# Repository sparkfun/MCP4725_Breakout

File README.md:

MCP4725_Breakout
================
[  
*Breakout Board for MCP4725 I2C DAC (BOB-12918)*](https://www.sparkfun.com/products/12918)

The MCP4725 is an I<sup>2</sup>C controlled Digital-to-Analog converter (DAC). It allows you to send an analog signal from a digital source.

Repository Contents
-------------------
* **/Hardware** - Eagle PCB layout files
* **/Production** - Test bed files and production panel files

Version History
---------------
* [BOB-08736](https://www.sparkfun.com/products/8736) -Version 1.3. Now retired. 

License Information
-------------------
The hardware is released under [Creative Commons ShareAlike 4.0 International](https://creativecommons.org/licenses/by-sa/4.0/).
The code is beerware; if you see me (or any other SparkFun employee) at the local, and you've found our code helpful, please buy us a round!

Distributed as-is; no warranty is given.

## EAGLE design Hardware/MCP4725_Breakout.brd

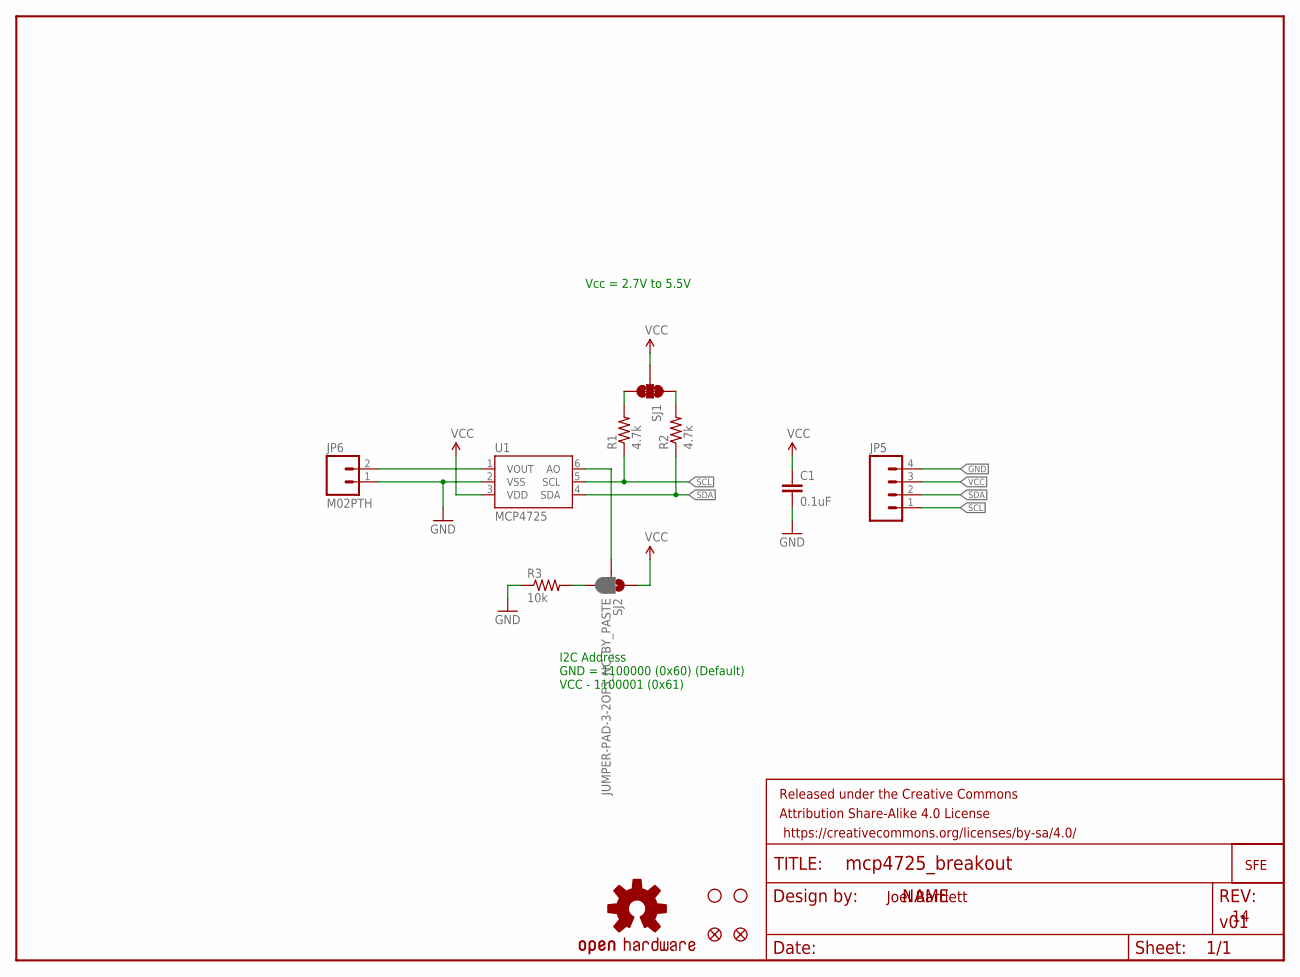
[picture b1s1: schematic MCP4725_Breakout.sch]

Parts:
C1: 0.1uF; 0603-CAP
FID1, FID2: FIDUCIAL1X2; FIDUCIAL-1X2
FRAME2: FRAME-LETTER; CREATIVE_COMMONS
GND: LOGO-SFESK; SFE-LOGO-FLAME
JP5: M04PTH; 1X04
JP6: M02PTH; 1X02
LOGO1: OSHW-LOGOS; OSHW-LOGO-S
R1, R2: 4.7k; 0603-RES
R3: 10k; 0603-RES
SJ1: JUMPER-PAD-3-NC_BY_TRACE; PAD-JUMPER-3-3OF3_NC_BY_TRACE_YES_SILK_FULL_BOX
SJ2: JUMPER-PAD-3-2OF3_NC_BY_PASTE; PAD-JUMPER-3-2OF3_NC_BY_PASTE_YES_SILK_FULL_BOX
STANDOFF1, STANDOFF2: STAND-OFF
U1: MCP4725; SOT23-6

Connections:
GND: C1.2, JP5.4, JP6.1, R3.1, U1.2 (VSS)
unnamed: R2.2, SJ1.1
unnamed: R1.2, SJ1.3
unnamed: SJ2.2, U1.6 (AO)
unnamed: R3.2, SJ2.3
SCL: JP5.1, R1.1, U1.5 (SCL)
SDA: JP5.2, R2.1, U1.4 (SDA)
VCC: C1.1, JP5.3, SJ1.2, SJ2.1, U1.3 (VDD)
VOUT: JP6.2, U1.1 (VOUT)

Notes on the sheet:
I2C Address GND = 1100000 (0x60) (Default) VCC - 1100001 (0x61)
Joel Bartlett
Vcc = 2.7V to 5.5V

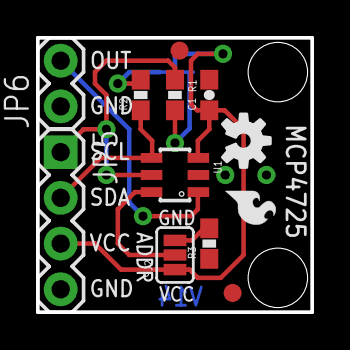
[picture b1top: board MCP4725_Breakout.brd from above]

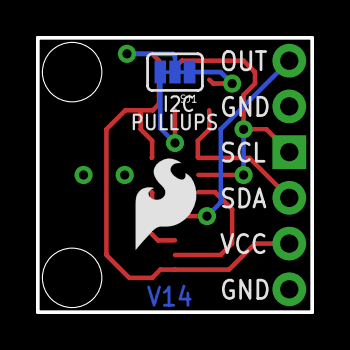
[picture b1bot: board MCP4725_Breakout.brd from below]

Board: 2 copper layers, 15.2 x 15.2 mm, 17 parts (2 on the bottom side), 9 nets.

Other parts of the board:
U$3: SFE_LOGO_FLAME_.2

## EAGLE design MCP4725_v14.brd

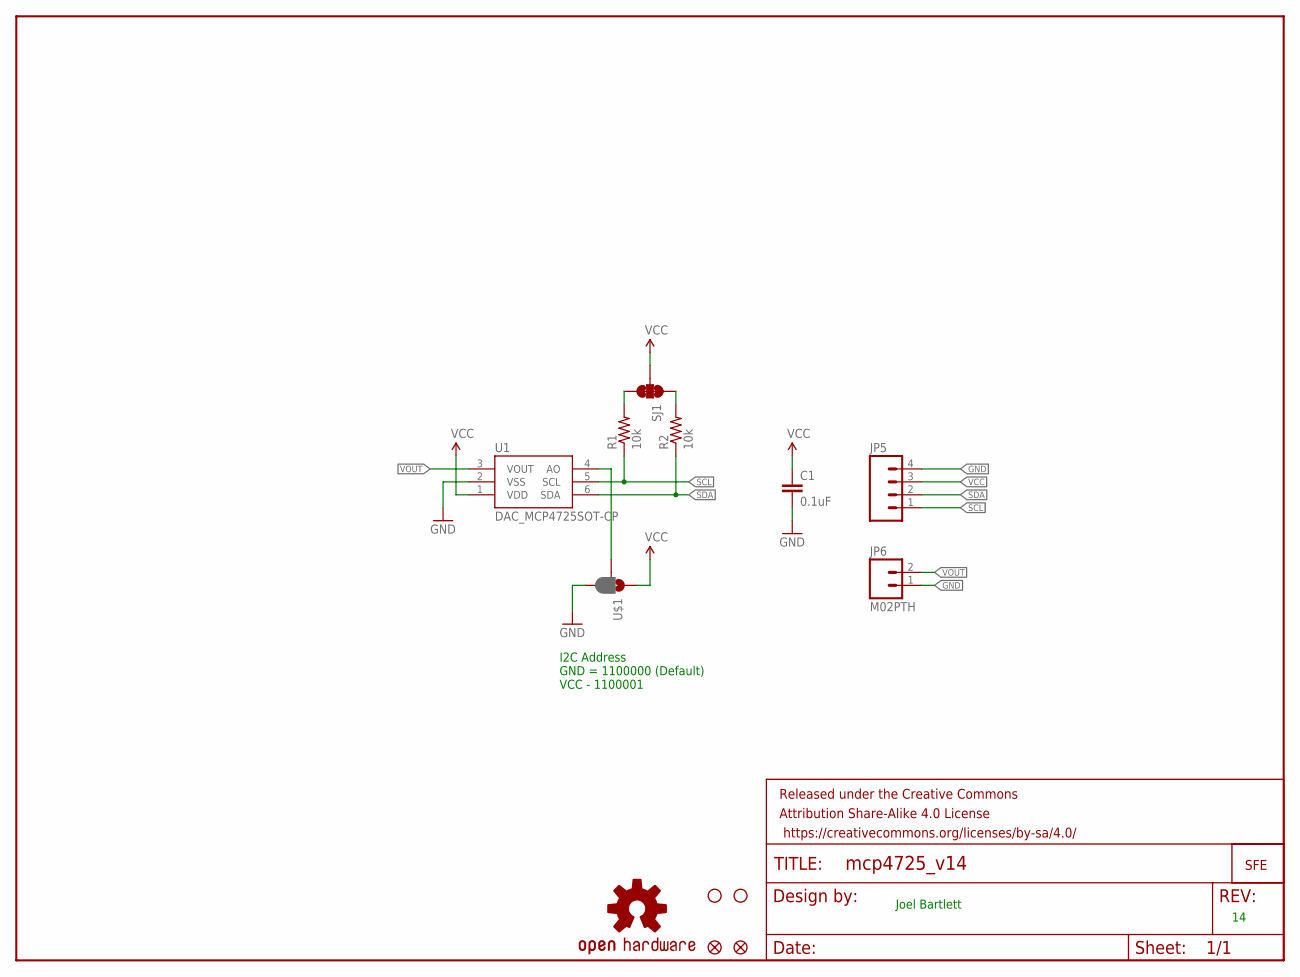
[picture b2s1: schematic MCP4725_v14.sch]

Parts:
C1: 0.1uF; 0603-CAP
FRAME2: FRAME-LETTER; CREATIVE_COMMONS
GND: LOGO-SFESK; SFE-LOGO-FLAME
JP2, JP3: FIDUCIALUFIDUCIAL; MICRO-FIDUCIAL
JP5: M04PTH; 1X04
JP6: M02PTH; 1X02
LOGO1: OSHW-LOGOS; OSHW-LOGO-S
R1, R2: 10k; 0603-RES
SJ1: JUMPER-PAD-3-NC_BY_TRACE; PAD-JUMPER-3-3OF3_NC_BY_TRACE_YES_SILK_FULL_BOX
STANDOFF1, STANDOFF2: STAND-OFF
U1: DAC_MCP4725SOT-CP; SOT23-6-MCP4725
U$1: JUMPER-PAD-3-2OF3_NC_BY_PASTE; PAD-JUMPER-3-2OF3_NC_BY_PASTE_YES_SILK_FULL_BOX

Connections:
GND: C1.2, JP5.4, JP6.1, U1.2 (VSS), U$1.3
unnamed: R2.2, SJ1.1
unnamed: R1.2, SJ1.3
unnamed: U1.4 (AO), U$1.2
SCL: JP5.1, R1.1, U1.5 (SCL)
SDA: JP5.2, R2.1, U1.6 (SDA)
VCC: C1.1, JP5.3, SJ1.2, U1.1 (VDD), U$1.1
VOUT: JP6.2, U1.3 (VOUT)

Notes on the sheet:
I2C Address GND = 1100000 (Default) VCC - 1100001
Joel Bartlett

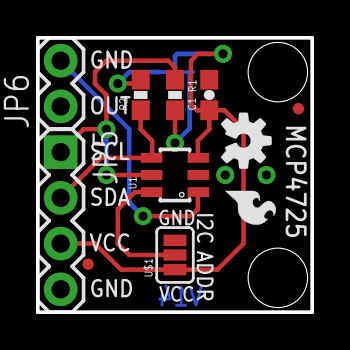
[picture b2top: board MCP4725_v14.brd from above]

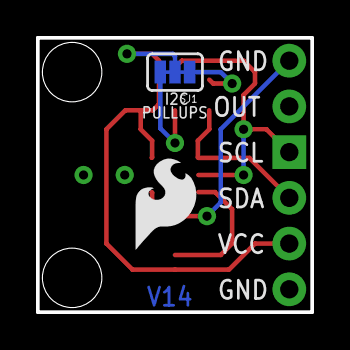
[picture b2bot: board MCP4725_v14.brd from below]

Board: 2 copper layers, 15.2 x 15.2 mm, 16 parts (2 on the bottom side), 8 nets.

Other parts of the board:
U$3: SFE_LOGO_FLAME_.2

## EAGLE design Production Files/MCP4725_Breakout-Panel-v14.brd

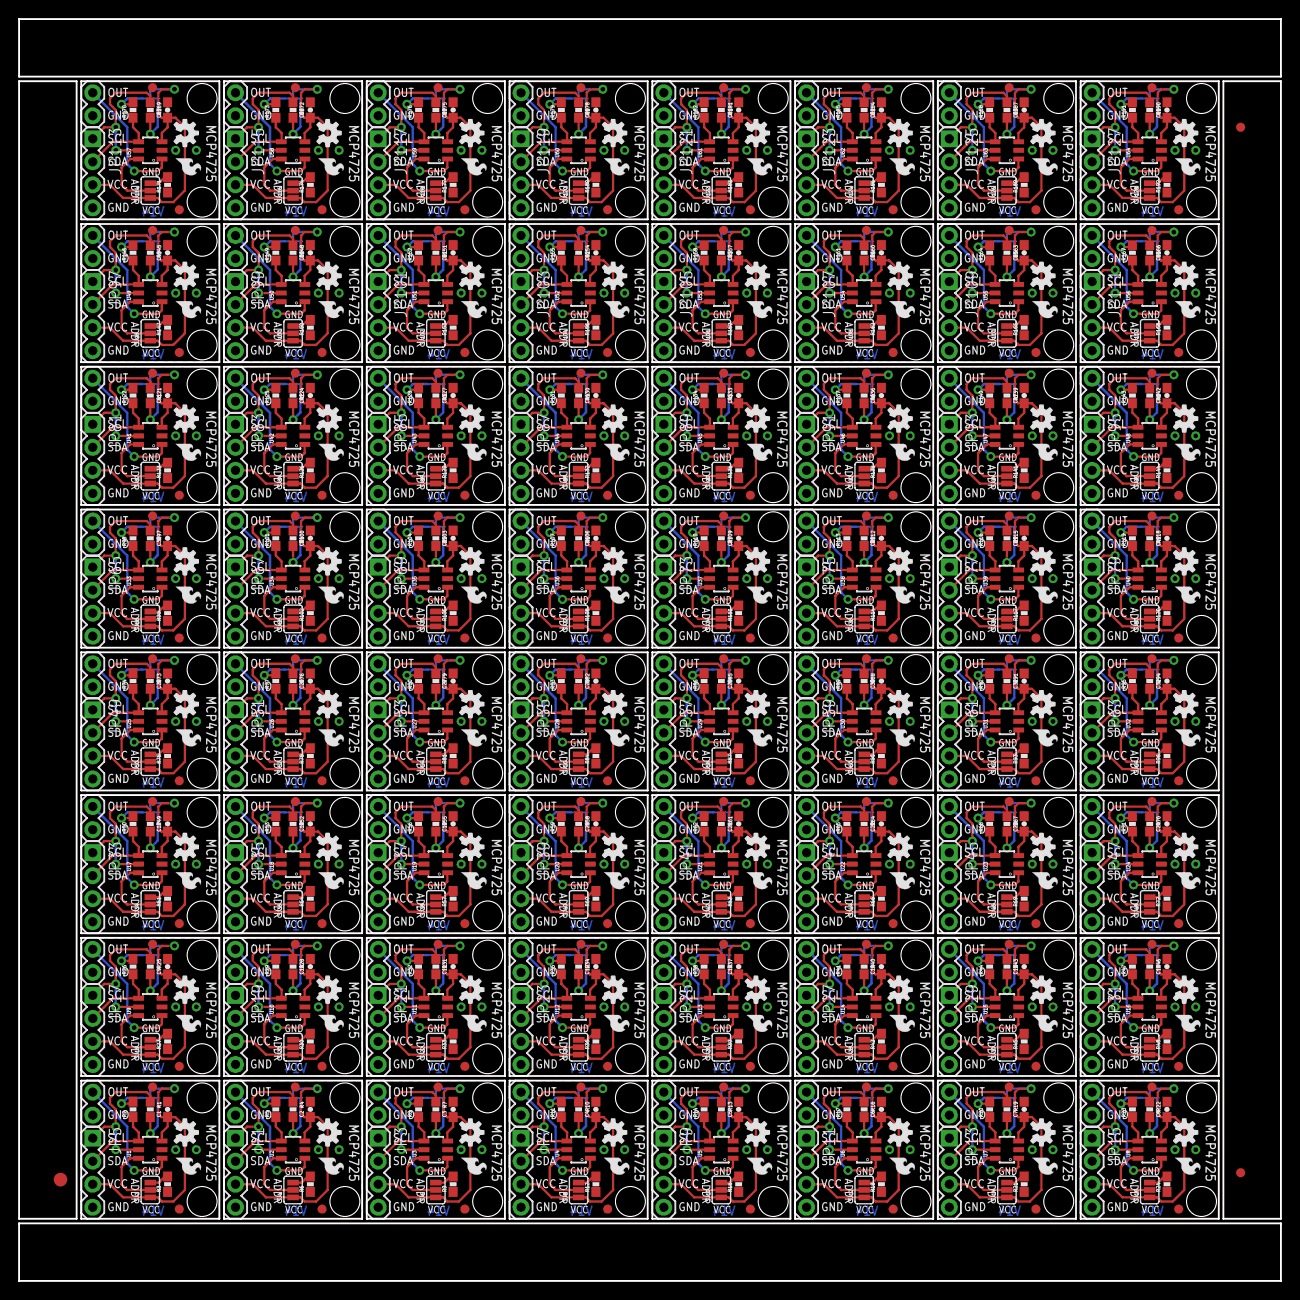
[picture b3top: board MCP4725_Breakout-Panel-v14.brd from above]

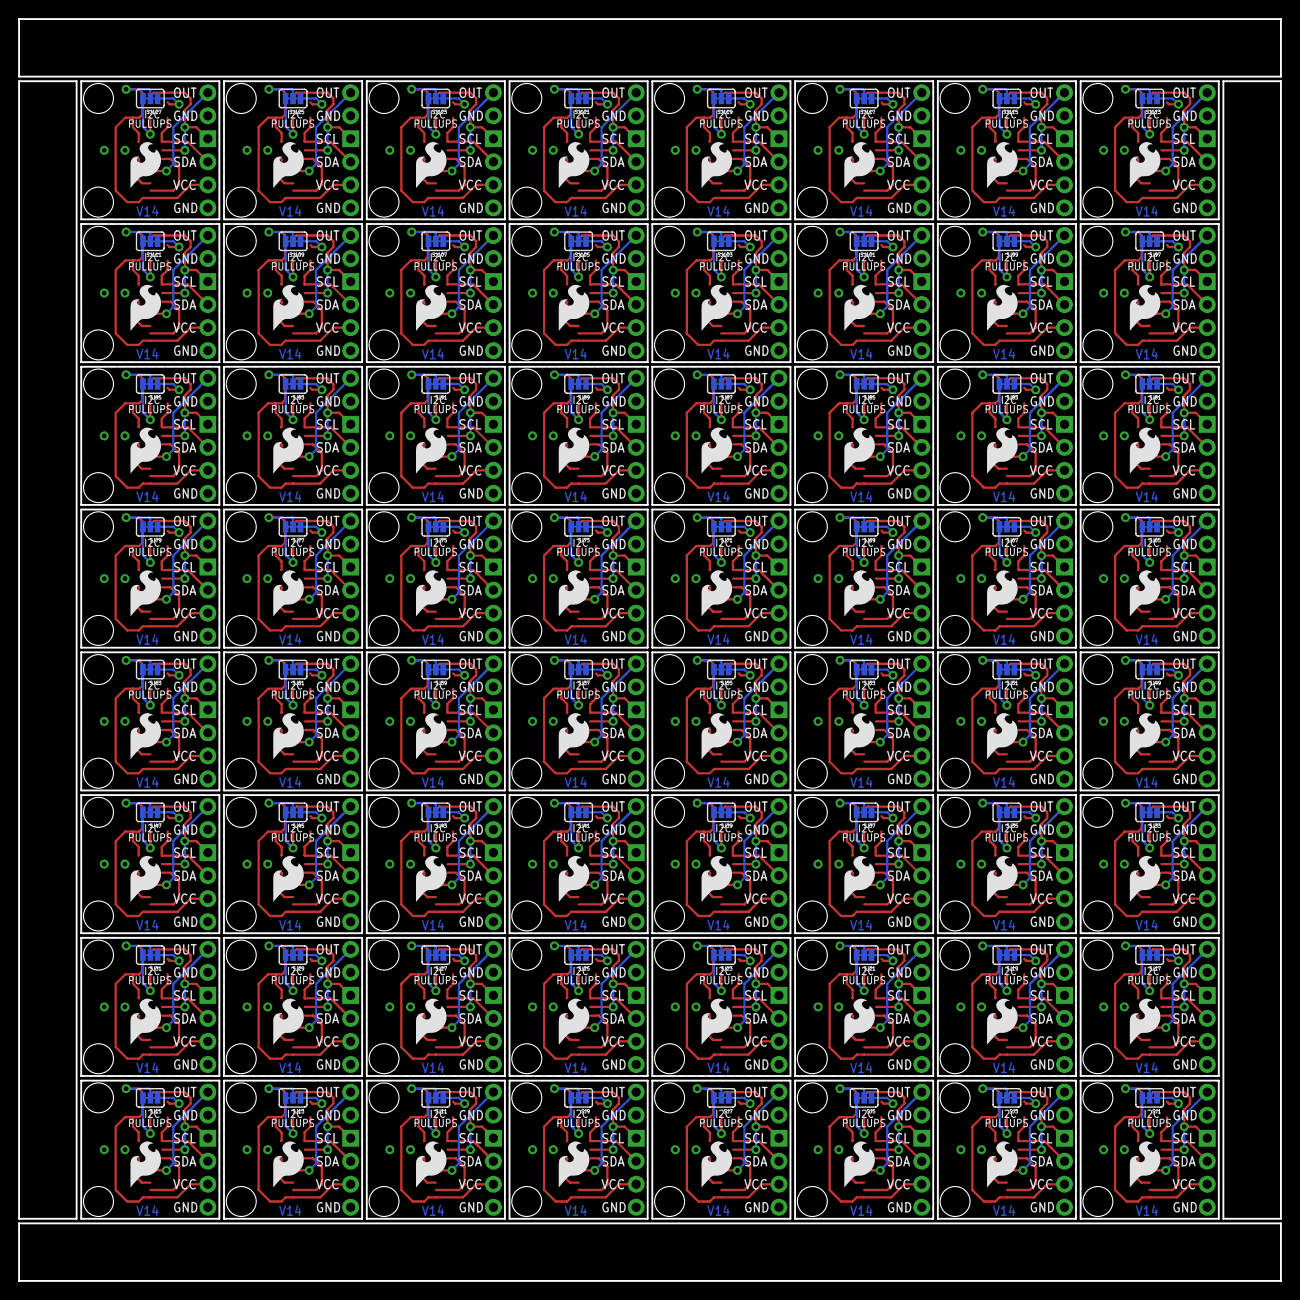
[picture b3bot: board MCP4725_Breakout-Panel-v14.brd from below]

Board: 2 copper layers, 139.2 x 139.2 mm, 1027 parts (128 on the bottom side), 576 nets.

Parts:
C1, C2, C3, C4, C5, C6, C7, C8, C9, C10, C11, C12, C13, C14, C15, C16, C17, C18, C19, C20, C21, C22, C23, C24, C25, C26, C27, C28, C29, C30, C31, C32, C33, C34, C35, C36, C37, C38, C39, C40, C41, C42, C43, C44, C45, C46, C47, C48, C49, C50, C51, C52, C53, C54, C55, C56, C57, C58, C59, C60, C61, C62, C63, C64: 0.1uF; 0603-CAP
E$1: FIDUCIAL-1.5X3
E$4, E$5: FIDUCIAL-1X2
FID1, FID2, FID3, FID4, FID5, FID6, FID7, FID8, FID9, FID10, FID11, FID12, FID13, FID14, FID15, FID16, FID17, FID18, FID19, FID20, FID21, FID22, FID23, FID24, FID25, FID26, FID27, FID28, FID29, FID30, FID31, FID32, FID33, FID34, FID35, FID36, FID37, FID38, FID39, FID40, FID41, FID42, FID43, FID44, FID45, FID46, FID47, FID48, FID49, FID50, FID51, FID52, FID53, FID54, FID55, FID56, FID57, FID58, FID59, FID60, FID61, FID62, FID63, FID64, FID65, FID66, FID67, FID68, FID69, FID70, FID71, FID72, FID73, FID74, FID75, FID76, FID77, FID78, FID79, FID80, FID81, FID82, FID83, FID84, FID85, FID86, FID87, FID88, FID89, FID90, FID91, FID92, FID93, FID94, FID95, FID96, FID97, FID98, FID99, FID100, FID101, FID102, FID103, FID104, FID105, FID106, FID107, FID108, FID109, FID110, FID111, FID112, FID113, FID114, FID115, FID116, FID117, FID118, FID119, FID120, FID121, FID122, FID123, FID124, FID125, FID126, FID127, FID128: FIDUCIAL1X2; FIDUCIAL-1X2
GND, GND1, GND2, GND3, GND4, GND5, GND6, GND7, GND8, GND9, GND10, GND11, GND12, GND13, GND14, GND15, GND16, GND17, GND18, GND19, GND20, GND21, GND22, GND23, GND24, GND25, GND26, GND27, GND28, GND29, GND30, GND31, GND32, GND33, GND34, GND35, GND36, GND37, GND38, GND39, GND40, GND41, GND42, GND43, GND44, GND45, GND46, GND47, GND48, GND49, GND50, GND51, GND52, GND53, GND54, GND55, GND56, GND57, GND58, GND59, GND60, GND61, GND62, GND63: LOGO-SFESK; SFE-LOGO-FLAME
JP1, JP3, JP5, JP7, JP9, JP11, JP13, JP15, JP17, JP19, JP21, JP23, JP25, JP27, JP29, JP31, JP33, JP35, JP37, JP39, JP41, JP43, JP45, JP47, JP49, JP51, JP53, JP55, JP57, JP59, JP61, JP63, JP65, JP67, JP69, JP71, JP73, JP75, JP77, JP79, JP81, JP83, JP85, JP87, JP89, JP91, JP93, JP95, JP97, JP99, JP101, JP103, JP105, JP107, JP109, JP111, JP113, JP115, JP117, JP119, JP121, JP123, JP125, JP127: 1X04
JP2, JP4, JP6, JP8, JP10, JP12, JP14, JP16, JP18, JP20, JP22, JP24, JP26, JP28, JP30, JP32, JP34, JP36, JP38, JP40, JP42, JP44, JP46, JP48, JP50, JP52, JP54, JP56, JP58, JP60, JP62, JP64, JP66, JP68, JP70, JP72, JP74, JP76, JP78, JP80, JP82, JP84, JP86, JP88, JP90, JP92, JP94, JP96, JP98, JP100, JP102, JP104, JP106, JP108, JP110, JP112, JP114, JP116, JP118, JP120, JP122, JP124, JP126, JP128: M02PTH; 1X02
LOGO1, LOGO2, LOGO3, LOGO4, LOGO5, LOGO6, LOGO7, LOGO8, LOGO9, LOGO10, LOGO11, LOGO12, LOGO13, LOGO14, LOGO15, LOGO16, LOGO17, LOGO18, LOGO19, LOGO20, LOGO21, LOGO22, LOGO23, LOGO24, LOGO25, LOGO26, LOGO27, LOGO28, LOGO29, LOGO30, LOGO31, LOGO32, LOGO33, LOGO34, LOGO35, LOGO36, LOGO37, LOGO38, LOGO39, LOGO40, LOGO41, LOGO42, LOGO43, LOGO44, LOGO45, LOGO46, LOGO47, LOGO48, LOGO49, LOGO50, LOGO51, LOGO52, LOGO53, LOGO54, LOGO55, LOGO56, LOGO57, LOGO58, LOGO59, LOGO60, LOGO61, LOGO62, LOGO63, LOGO64: OSHW-LOGOS; OSHW-LOGO-S
R1, R2, R4, R5, R7, R8, R10, R11, R13, R14, R16, R17, R19, R20, R22, R23, R25, R26, R28, R29, R31, R32, R34, R35, R37, R38, R40, R41, R43, R44, R46, R47, R49, R50, R52, R53, R55, R56, R58, R59, R61, R62, R64, R65, R67, R68, R70, R71, R73, R74, R76, R77, R79, R80, R82, R83, R85, R86, R88, R89, R91, R92, R94, R95, R97, R98, R100, R101, R103, R104, R106, R107, R109, R110, R112, R113, R115, R116, R118, R119, R121, R122, R124, R125, R127, R128, R130, R131, R133, R134, R136, R137, R139, R140, R142, R143, R145, R146, R148, R149, R151, R152, R154, R155, R157, R158, R160, R161, R163, R164, R166, R167, R169, R170, R172, R173, R175, R176, R178, R179, R181, R182, R184, R185, R187, R188, R190, R191: 4.7k; 0603-RES
R3, R6, R9, R12, R15, R18, R21, R24, R27, R30, R33, R36, R39, R42, R45, R48, R51, R54, R57, R60, R63, R66, R69, R72, R75, R78, R81, R84, R87, R90, R93, R96, R99, R102, R105, R108, R111, R114, R117, R120, R123, R126, R129, R132, R135, R138, R141, R144, R147, R150, R153, R156, R159, R162, R165, R168, R171, R174, R177, R180, R183, R186, R189, R192: 10k; 0603-RES
SJ1, SJ3, SJ5, SJ7, SJ9, SJ11, SJ13, SJ15, SJ17, SJ19, SJ21, SJ23, SJ25, SJ27, SJ29, SJ31, SJ33, SJ35, SJ37, SJ39, SJ41, SJ43, SJ45, SJ47, SJ49, SJ51, SJ53, SJ55, SJ57, SJ59, SJ61, SJ63, SJ65, SJ67, SJ69, SJ71, SJ73, SJ75, SJ77, SJ79, SJ81, SJ83, SJ85, SJ87, SJ89, SJ91, SJ93, SJ95, SJ97, SJ99, SJ101, SJ103, SJ105, SJ107, SJ109, SJ111, SJ113, SJ115, SJ117, SJ119, SJ121, SJ123, SJ125, SJ127: PAD-JUMPER-3-3OF3_NC_BY_TRACE_YES_SILK_FULL_BOX
SJ2, SJ4, SJ6, SJ8, SJ10, SJ12, SJ14, SJ16, SJ18, SJ20, SJ22, SJ24, SJ26, SJ28, SJ30, SJ32, SJ34, SJ36, SJ38, SJ40, SJ42, SJ44, SJ46, SJ48, SJ50, SJ52, SJ54, SJ56, SJ58, SJ60, SJ62, SJ64, SJ66, SJ68, SJ70, SJ72, SJ74, SJ76, SJ78, SJ80, SJ82, SJ84, SJ86, SJ88, SJ90, SJ92, SJ94, SJ96, SJ98, SJ100, SJ102, SJ104, SJ106, SJ108, SJ110, SJ112, SJ114, SJ116, SJ118, SJ120, SJ122, SJ124, SJ126, SJ128: PAD-JUMPER-3-2OF3_NC_BY_PASTE_YES_SILK_FULL_BOX
STANDOFF1, STANDOFF2, STANDOFF3, STANDOFF4, STANDOFF5, STANDOFF6, STANDOFF7, STANDOFF8, STANDOFF9, STANDOFF10, STANDOFF11, STANDOFF12, STANDOFF13, STANDOFF14, STANDOFF15, STANDOFF16, STANDOFF17, STANDOFF18, STANDOFF19, STANDOFF20, STANDOFF21, STANDOFF22, STANDOFF23, STANDOFF24, STANDOFF25, STANDOFF26, STANDOFF27, STANDOFF28, STANDOFF29, STANDOFF30, STANDOFF31, STANDOFF32, STANDOFF33, STANDOFF34, STANDOFF35, STANDOFF36, STANDOFF37, STANDOFF38, STANDOFF39, STANDOFF40, STANDOFF41, STANDOFF42, STANDOFF43, STANDOFF44, STANDOFF45, STANDOFF46, STANDOFF47, STANDOFF48, STANDOFF49, STANDOFF50, STANDOFF51, STANDOFF52, STANDOFF53, STANDOFF54, STANDOFF55, STANDOFF56, STANDOFF57, STANDOFF58, STANDOFF59, STANDOFF60, STANDOFF61, STANDOFF62, STANDOFF63, STANDOFF64, STANDOFF65, STANDOFF66, STANDOFF67, STANDOFF68, STANDOFF69, STANDOFF70, STANDOFF71, STANDOFF72, STANDOFF73, STANDOFF74, STANDOFF75, STANDOFF76, STANDOFF77, STANDOFF78, STANDOFF79, STANDOFF80, STANDOFF81, STANDOFF82, STANDOFF83, STANDOFF84, STANDOFF85, STANDOFF86, STANDOFF87, STANDOFF88, STANDOFF89, STANDOFF90, STANDOFF91, STANDOFF92, STANDOFF93, STANDOFF94, STANDOFF95, STANDOFF96, STANDOFF97, STANDOFF98, STANDOFF99, STANDOFF100, STANDOFF101, STANDOFF102, STANDOFF103, STANDOFF104, STANDOFF105, STANDOFF106, STANDOFF107, STANDOFF108, STANDOFF109, STANDOFF110, STANDOFF111, STANDOFF112, STANDOFF113, STANDOFF114, STANDOFF115, STANDOFF116, STANDOFF117, STANDOFF118, STANDOFF119, STANDOFF120, STANDOFF121, STANDOFF122, STANDOFF123, STANDOFF124, STANDOFF125, STANDOFF126, STANDOFF127, STANDOFF128: STAND-OFF
U1, U2, U3, U4, U5, U6, U7, U8, U9, U10, U11, U12, U13, U14, U15, U16, U17, U18, U19, U20, U21, U22, U23, U24, U25, U26, U27, U28, U29, U30, U31, U32, U33, U34, U35, U36, U37, U38, U39, U40, U41, U42, U43, U44, U45, U46, U47, U48, U49, U50, U51, U52, U53, U54, U55, U56, U57, U58, U59, U60, U61, U62, U63, U64: DAC_MCP4725SOT-CP; SOT23-6-MCP4725
U$1, U$2, U$3, U$4, U$5, U$6, U$7, U$8, U$9, U$10, U$11, U$12, U$13, U$14, U$15, U$16, U$17, U$18, U$19, U$20, U$21, U$22, U$23, U$24, U$25, U$26, U$27, U$28, U$29, U$30, U$31, U$32, U$33, U$34, U$35, U$36, U$37, U$38, U$39, U$40, U$41, U$42, U$43, U$44, U$45, U$46, U$47, U$48, U$49, U$50, U$51, U$52, U$53, U$54, U$55, U$56, U$57, U$58, U$59, U$60, U$61, U$62, U$63, U$64: SFE_LOGO_FLAME_.2

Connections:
GND: C1.2, JP5.4, JP6.1, R3.1, U1.2
GND1: C2.2, JP1.4, JP2.1, R6.1, U2.2
GND2: C3.2, JP3.4, JP4.1, R9.1, U3.2
GND3: C4.2, JP7.4, JP8.1, R12.1, U4.2
GND4: C5.2, JP9.4, JP10.1, R15.1, U5.2
GND5: C6.2, JP11.4, JP12.1, R18.1, U6.2
GND6: C7.2, JP13.4, JP14.1, R21.1, U7.2
GND7: C8.2, JP15.4, JP16.1, R24.1, U8.2
GND8: C9.2, JP17.4, JP18.1, R27.1, U9.2
GND9: C10.2, JP19.4, JP20.1, R30.1, U10.2
GND10: C11.2, JP21.4, JP22.1, R33.1, U11.2
GND11: C12.2, JP23.4, JP24.1, R36.1, U12.2
GND12: C13.2, JP25.4, JP26.1, R39.1, U13.2
GND13: C14.2, JP27.4, JP28.1, R42.1, U14.2
GND14: C15.2, JP29.4, JP30.1, R45.1, U15.2
GND15: C16.2, JP31.4, JP32.1, R48.1, U16.2
GND16: C17.2, JP33.4, JP34.1, R51.1, U17.2
GND17: C18.2, JP35.4, JP36.1, R54.1, U18.2
GND18: C19.2, JP37.4, JP38.1, R57.1, U19.2
GND19: C20.2, JP39.4, JP40.1, R60.1, U20.2
GND20: C21.2, JP41.4, JP42.1, R63.1, U21.2
GND21: C22.2, JP43.4, JP44.1, R66.1, U22.2
GND22: C23.2, JP45.4, JP46.1, R69.1, U23.2
GND23: C24.2, JP47.4, JP48.1, R72.1, U24.2
GND24: C25.2, JP49.4, JP50.1, R75.1, U25.2
GND25: C26.2, JP51.4, JP52.1, R78.1, U26.2
GND26: C27.2, JP53.4, JP54.1, R81.1, U27.2
GND27: C28.2, JP55.4, JP56.1, R84.1, U28.2
GND28: C29.2, JP57.4, JP58.1, R87.1, U29.2
GND29: C30.2, JP59.4, JP60.1, R90.1, U30.2
GND30: C31.2, JP61.4, JP62.1, R93.1, U31.2
GND31: C32.2, JP63.4, JP64.1, R96.1, U32.2
GND32: C33.2, JP65.4, JP66.1, R99.1, U33.2
GND33: C34.2, JP67.4, JP68.1, R102.1, U34.2
GND34: C35.2, JP69.4, JP70.1, R105.1, U35.2
GND35: C36.2, JP71.4, JP72.1, R108.1, U36.2
GND36: C37.2, JP73.4, JP74.1, R111.1, U37.2
GND37: C38.2, JP75.4, JP76.1, R114.1, U38.2
GND38: C39.2, JP77.4, JP78.1, R117.1, U39.2
GND39: C40.2, JP79.4, JP80.1, R120.1, U40.2
GND40: C41.2, JP81.4, JP82.1, R123.1, U41.2
GND41: C42.2, JP83.4, JP84.1, R126.1, U42.2
GND42: C43.2, JP85.4, JP86.1, R129.1, U43.2
GND43: C44.2, JP87.4, JP88.1, R132.1, U44.2
GND44: C45.2, JP89.4, JP90.1, R135.1, U45.2
GND45: C46.2, JP91.4, JP92.1, R138.1, U46.2
GND46: C47.2, JP93.4, JP94.1, R141.1, U47.2
GND47: C48.2, JP95.4, JP96.1, R144.1, U48.2
GND48: C49.2, JP97.4, JP98.1, R147.1, U49.2
GND49: C50.2, JP99.4, JP100.1, R150.1, U50.2
GND50: C51.2, JP101.4, JP102.1, R153.1, U51.2
GND51: C52.2, JP103.4, JP104.1, R156.1, U52.2
GND52: C53.2, JP105.4, JP106.1, R159.1, U53.2
GND53: C54.2, JP107.4, JP108.1, R162.1, U54.2
GND54: C55.2, JP109.4, JP110.1, R165.1, U55.2
GND55: C56.2, JP111.4, JP112.1, R168.1, U56.2
GND56: C57.2, JP113.4, JP114.1, R171.1, U57.2
GND57: C58.2, JP115.4, JP116.1, R174.1, U58.2
GND58: C59.2, JP117.4, JP118.1, R177.1, U59.2
GND59: C60.2, JP119.4, JP120.1, R180.1, U60.2
GND60: C61.2, JP121.4, JP122.1, R183.1, U61.2
GND61: C62.2, JP123.4, JP124.1, R186.1, U62.2
GND62: C63.2, JP125.4, JP126.1, R189.1, U63.2
GND63: C64.2, JP127.4, JP128.1, R192.1, U64.2
unnamed: R2.2, SJ1.1
unnamed: R1.2, SJ1.3
unnamed: SJ2.2, U1.4
unnamed: R3.2, SJ2.3
unnamed: R5.2, SJ3.1
unnamed: R4.2, SJ3.3
unnamed: SJ4.2, U2.4
unnamed: R6.2, SJ4.3
unnamed: R8.2, SJ5.1
unnamed: R7.2, SJ5.3
unnamed: SJ6.2, U3.4
unnamed: R9.2, SJ6.3
unnamed: R11.2, SJ7.1
unnamed: R10.2, SJ7.3
unnamed: SJ8.2, U4.4
unnamed: R12.2, SJ8.3
unnamed: R14.2, SJ9.1
unnamed: R13.2, SJ9.3
unnamed: SJ10.2, U5.4
unnamed: R15.2, SJ10.3
unnamed: R17.2, SJ11.1
unnamed: R16.2, SJ11.3
unnamed: SJ12.2, U6.4
unnamed: R18.2, SJ12.3
unnamed: R20.2, SJ13.1
unnamed: R19.2, SJ13.3
unnamed: SJ14.2, U7.4
unnamed: R21.2, SJ14.3
unnamed: R23.2, SJ15.1
unnamed: R22.2, SJ15.3
unnamed: SJ16.2, U8.4
unnamed: R24.2, SJ16.3
unnamed: R26.2, SJ17.1
unnamed: R25.2, SJ17.3
unnamed: SJ18.2, U9.4
unnamed: R27.2, SJ18.3
unnamed: R29.2, SJ19.1
unnamed: R28.2, SJ19.3
unnamed: SJ20.2, U10.4
unnamed: R30.2, SJ20.3
unnamed: R32.2, SJ21.1
unnamed: R31.2, SJ21.3
unnamed: SJ22.2, U11.4
unnamed: R33.2, SJ22.3
unnamed: R35.2, SJ23.1
unnamed: R34.2, SJ23.3
unnamed: SJ24.2, U12.4
unnamed: R36.2, SJ24.3
unnamed: R38.2, SJ25.1
unnamed: R37.2, SJ25.3
unnamed: SJ26.2, U13.4
unnamed: R39.2, SJ26.3
unnamed: R41.2, SJ27.1
unnamed: R40.2, SJ27.3
unnamed: SJ28.2, U14.4
unnamed: R42.2, SJ28.3
unnamed: R44.2, SJ29.1
unnamed: R43.2, SJ29.3
unnamed: SJ30.2, U15.4
unnamed: R45.2, SJ30.3
unnamed: R47.2, SJ31.1
unnamed: R46.2, SJ31.3
unnamed: SJ32.2, U16.4
unnamed: R48.2, SJ32.3
unnamed: R50.2, SJ33.1
unnamed: R49.2, SJ33.3
unnamed: SJ34.2, U17.4
unnamed: R51.2, SJ34.3
unnamed: R53.2, SJ35.1
unnamed: R52.2, SJ35.3
unnamed: SJ36.2, U18.4
unnamed: R54.2, SJ36.3
unnamed: R56.2, SJ37.1
unnamed: R55.2, SJ37.3
unnamed: SJ38.2, U19.4
unnamed: R57.2, SJ38.3
unnamed: R59.2, SJ39.1
unnamed: R58.2, SJ39.3
unnamed: SJ40.2, U20.4
unnamed: R60.2, SJ40.3
unnamed: R62.2, SJ41.1
unnamed: R61.2, SJ41.3
unnamed: SJ42.2, U21.4
unnamed: R63.2, SJ42.3
unnamed: R65.2, SJ43.1
unnamed: R64.2, SJ43.3
unnamed: SJ44.2, U22.4
unnamed: R66.2, SJ44.3
unnamed: R68.2, SJ45.1
unnamed: R67.2, SJ45.3
unnamed: SJ46.2, U23.4
unnamed: R69.2, SJ46.3
unnamed: R71.2, SJ47.1
unnamed: R70.2, SJ47.3
unnamed: SJ48.2, U24.4
unnamed: R72.2, SJ48.3
unnamed: R74.2, SJ49.1
unnamed: R73.2, SJ49.3
unnamed: SJ50.2, U25.4
unnamed: R75.2, SJ50.3
unnamed: R77.2, SJ51.1
unnamed: R76.2, SJ51.3
unnamed: SJ52.2, U26.4
unnamed: R78.2, SJ52.3
unnamed: R80.2, SJ53.1
unnamed: R79.2, SJ53.3
unnamed: SJ54.2, U27.4
unnamed: R81.2, SJ54.3
unnamed: R83.2, SJ55.1
unnamed: R82.2, SJ55.3
unnamed: SJ56.2, U28.4
unnamed: R84.2, SJ56.3
unnamed: R86.2, SJ57.1
unnamed: R85.2, SJ57.3
unnamed: SJ58.2, U29.4
unnamed: R87.2, SJ58.3
unnamed: R89.2, SJ59.1
unnamed: R88.2, SJ59.3
unnamed: SJ60.2, U30.4
unnamed: R90.2, SJ60.3
unnamed: R92.2, SJ61.1
unnamed: R91.2, SJ61.3
unnamed: SJ62.2, U31.4
unnamed: R93.2, SJ62.3
unnamed: R95.2, SJ63.1
unnamed: R94.2, SJ63.3
unnamed: SJ64.2, U32.4
unnamed: R96.2, SJ64.3
unnamed: R98.2, SJ65.1
unnamed: R97.2, SJ65.3
unnamed: SJ66.2, U33.4
unnamed: R99.2, SJ66.3
unnamed: R101.2, SJ67.1
unnamed: R100.2, SJ67.3
unnamed: SJ68.2, U34.4
unnamed: R102.2, SJ68.3
unnamed: R104.2, SJ69.1
unnamed: R103.2, SJ69.3
unnamed: SJ70.2, U35.4
unnamed: R105.2, SJ70.3
unnamed: R107.2, SJ71.1
unnamed: R106.2, SJ71.3
unnamed: SJ72.2, U36.4
unnamed: R108.2, SJ72.3
unnamed: R110.2, SJ73.1
unnamed: R109.2, SJ73.3
unnamed: SJ74.2, U37.4
unnamed: R111.2, SJ74.3
unnamed: R113.2, SJ75.1
unnamed: R112.2, SJ75.3
unnamed: SJ76.2, U38.4
unnamed: R114.2, SJ76.3
unnamed: R116.2, SJ77.1
unnamed: R115.2, SJ77.3
unnamed: SJ78.2, U39.4
unnamed: R117.2, SJ78.3
unnamed: R119.2, SJ79.1
unnamed: R118.2, SJ79.3
unnamed: SJ80.2, U40.4
unnamed: R120.2, SJ80.3
unnamed: R122.2, SJ81.1
unnamed: R121.2, SJ81.3
unnamed: SJ82.2, U41.4
unnamed: R123.2, SJ82.3
unnamed: R125.2, SJ83.1
unnamed: R124.2, SJ83.3
unnamed: SJ84.2, U42.4
unnamed: R126.2, SJ84.3
unnamed: R128.2, SJ85.1
unnamed: R127.2, SJ85.3
unnamed: SJ86.2, U43.4
unnamed: R129.2, SJ86.3
unnamed: R131.2, SJ87.1
unnamed: R130.2, SJ87.3
unnamed: SJ88.2, U44.4
unnamed: R132.2, SJ88.3
unnamed: R134.2, SJ89.1
unnamed: R133.2, SJ89.3
unnamed: SJ90.2, U45.4
unnamed: R135.2, SJ90.3
unnamed: R137.2, SJ91.1
unnamed: R136.2, SJ91.3
unnamed: SJ92.2, U46.4
unnamed: R138.2, SJ92.3
unnamed: R140.2, SJ93.1
unnamed: R139.2, SJ93.3
unnamed: SJ94.2, U47.4
unnamed: R141.2, SJ94.3
unnamed: R143.2, SJ95.1
unnamed: R142.2, SJ95.3
unnamed: SJ96.2, U48.4
unnamed: R144.2, SJ96.3
unnamed: R146.2, SJ97.1
unnamed: R145.2, SJ97.3
unnamed: SJ98.2, U49.4
unnamed: R147.2, SJ98.3
unnamed: R149.2, SJ99.1
unnamed: R148.2, SJ99.3
unnamed: SJ100.2, U50.4
unnamed: R150.2, SJ100.3
unnamed: R152.2, SJ101.1
unnamed: R151.2, SJ101.3
unnamed: SJ102.2, U51.4
unnamed: R153.2, SJ102.3
unnamed: R155.2, SJ103.1
unnamed: R154.2, SJ103.3
unnamed: SJ104.2, U52.4
unnamed: R156.2, SJ104.3
unnamed: R158.2, SJ105.1
unnamed: R157.2, SJ105.3
unnamed: SJ106.2, U53.4
unnamed: R159.2, SJ106.3
unnamed: R161.2, SJ107.1
unnamed: R160.2, SJ107.3
unnamed: SJ108.2, U54.4
unnamed: R162.2, SJ108.3
unnamed: R164.2, SJ109.1
unnamed: R163.2, SJ109.3
unnamed: SJ110.2, U55.4
unnamed: R165.2, SJ110.3
unnamed: R167.2, SJ111.1
unnamed: R166.2, SJ111.3
unnamed: SJ112.2, U56.4
unnamed: R168.2, SJ112.3
unnamed: R170.2, SJ113.1
unnamed: R169.2, SJ113.3
unnamed: SJ114.2, U57.4
unnamed: R171.2, SJ114.3
unnamed: R173.2, SJ115.1
unnamed: R172.2, SJ115.3
unnamed: SJ116.2, U58.4
unnamed: R174.2, SJ116.3
unnamed: R176.2, SJ117.1
unnamed: R175.2, SJ117.3
unnamed: SJ118.2, U59.4
unnamed: R177.2, SJ118.3
unnamed: R179.2, SJ119.1
unnamed: R178.2, SJ119.3
unnamed: SJ120.2, U60.4
unnamed: R180.2, SJ120.3
unnamed: R182.2, SJ121.1
unnamed: R181.2, SJ121.3
unnamed: SJ122.2, U61.4
unnamed: R183.2, SJ122.3
unnamed: R185.2, SJ123.1
unnamed: R184.2, SJ123.3
unnamed: SJ124.2, U62.4
unnamed: R186.2, SJ124.3
unnamed: R188.2, SJ125.1
unnamed: R187.2, SJ125.3
unnamed: SJ126.2, U63.4
unnamed: R189.2, SJ126.3
unnamed: R191.2, SJ127.1
unnamed: R190.2, SJ127.3
unnamed: SJ128.2, U64.4
unnamed: R192.2, SJ128.3
SCL: JP5.1, R1.1, U1.5
SCL1: JP1.1, R4.1, U2.5
SCL2: JP3.1, R7.1, U3.5
SCL3: JP7.1, R10.1, U4.5
SCL4: JP9.1, R13.1, U5.5
SCL5: JP11.1, R16.1, U6.5
SCL6: JP13.1, R19.1, U7.5
SCL7: JP15.1, R22.1, U8.5
SCL8: JP17.1, R25.1, U9.5
SCL9: JP19.1, R28.1, U10.5
SCL10: JP21.1, R31.1, U11.5
SCL11: JP23.1, R34.1, U12.5
SCL12: JP25.1, R37.1, U13.5
SCL13: JP27.1, R40.1, U14.5
SCL14: JP29.1, R43.1, U15.5
SCL15: JP31.1, R46.1, U16.5
SCL16: JP33.1, R49.1, U17.5
SCL17: JP35.1, R52.1, U18.5
SCL18: JP37.1, R55.1, U19.5
SCL19: JP39.1, R58.1, U20.5
SCL20: JP41.1, R61.1, U21.5
SCL21: JP43.1, R64.1, U22.5
SCL22: JP45.1, R67.1, U23.5
SCL23: JP47.1, R70.1, U24.5
SCL24: JP49.1, R73.1, U25.5
SCL25: JP51.1, R76.1, U26.5
SCL26: JP53.1, R79.1, U27.5
SCL27: JP55.1, R82.1, U28.5
SCL28: JP57.1, R85.1, U29.5
SCL29: JP59.1, R88.1, U30.5
SCL30: JP61.1, R91.1, U31.5
SCL31: JP63.1, R94.1, U32.5
SCL32: JP65.1, R97.1, U33.5
SCL33: JP67.1, R100.1, U34.5
SCL34: JP69.1, R103.1, U35.5
SCL35: JP71.1, R106.1, U36.5
SCL36: JP73.1, R109.1, U37.5
SCL37: JP75.1, R112.1, U38.5
SCL38: JP77.1, R115.1, U39.5
SCL39: JP79.1, R118.1, U40.5
SCL40: JP81.1, R121.1, U41.5
SCL41: JP83.1, R124.1, U42.5
SCL42: JP85.1, R127.1, U43.5
SCL43: JP87.1, R130.1, U44.5
SCL44: JP89.1, R133.1, U45.5
SCL45: JP91.1, R136.1, U46.5
SCL46: JP93.1, R139.1, U47.5
SCL47: JP95.1, R142.1, U48.5
SCL48: JP97.1, R145.1, U49.5
SCL49: JP99.1, R148.1, U50.5
SCL50: JP101.1, R151.1, U51.5
SCL51: JP103.1, R154.1, U52.5
SCL52: JP105.1, R157.1, U53.5
SCL53: JP107.1, R160.1, U54.5
SCL54: JP109.1, R163.1, U55.5
SCL55: JP111.1, R166.1, U56.5
SCL56: JP113.1, R169.1, U57.5
SCL57: JP115.1, R172.1, U58.5
SCL58: JP117.1, R175.1, U59.5
SCL59: JP119.1, R178.1, U60.5
SCL60: JP121.1, R181.1, U61.5
SCL61: JP123.1, R184.1, U62.5
SCL62: JP125.1, R187.1, U63.5
SCL63: JP127.1, R190.1, U64.5
SDA: JP5.2, R2.1, U1.6
SDA1: JP1.2, R5.1, U2.6
SDA2: JP3.2, R8.1, U3.6
SDA3: JP7.2, R11.1, U4.6
SDA4: JP9.2, R14.1, U5.6
SDA5: JP11.2, R17.1, U6.6
SDA6: JP13.2, R20.1, U7.6
SDA7: JP15.2, R23.1, U8.6
SDA8: JP17.2, R26.1, U9.6
SDA9: JP19.2, R29.1, U10.6
SDA10: JP21.2, R32.1, U11.6
SDA11: JP23.2, R35.1, U12.6
SDA12: JP25.2, R38.1, U13.6
SDA13: JP27.2, R41.1, U14.6
SDA14: JP29.2, R44.1, U15.6
SDA15: JP31.2, R47.1, U16.6
SDA16: JP33.2, R50.1, U17.6
SDA17: JP35.2, R53.1, U18.6
SDA18: JP37.2, R56.1, U19.6
SDA19: JP39.2, R59.1, U20.6
SDA20: JP41.2, R62.1, U21.6
SDA21: JP43.2, R65.1, U22.6
SDA22: JP45.2, R68.1, U23.6
SDA23: JP47.2, R71.1, U24.6
SDA24: JP49.2, R74.1, U25.6
SDA25: JP51.2, R77.1, U26.6
SDA26: JP53.2, R80.1, U27.6
SDA27: JP55.2, R83.1, U28.6
SDA28: JP57.2, R86.1, U29.6
SDA29: JP59.2, R89.1, U30.6
SDA30: JP61.2, R92.1, U31.6
SDA31: JP63.2, R95.1, U32.6
SDA32: JP65.2, R98.1, U33.6
SDA33: JP67.2, R101.1, U34.6
SDA34: JP69.2, R104.1, U35.6
SDA35: JP71.2, R107.1, U36.6
SDA36: JP73.2, R110.1, U37.6
SDA37: JP75.2, R113.1, U38.6
SDA38: JP77.2, R116.1, U39.6
SDA39: JP79.2, R119.1, U40.6
SDA40: JP81.2, R122.1, U41.6
SDA41: JP83.2, R125.1, U42.6
SDA42: JP85.2, R128.1, U43.6
SDA43: JP87.2, R131.1, U44.6
SDA44: JP89.2, R134.1, U45.6
SDA45: JP91.2, R137.1, U46.6
SDA46: JP93.2, R140.1, U47.6
SDA47: JP95.2, R143.1, U48.6
SDA48: JP97.2, R146.1, U49.6
SDA49: JP99.2, R149.1, U50.6
SDA50: JP101.2, R152.1, U51.6
SDA51: JP103.2, R155.1, U52.6
SDA52: JP105.2, R158.1, U53.6
SDA53: JP107.2, R161.1, U54.6
SDA54: JP109.2, R164.1, U55.6
SDA55: JP111.2, R167.1, U56.6
SDA56: JP113.2, R170.1, U57.6
SDA57: JP115.2, R173.1, U58.6
SDA58: JP117.2, R176.1, U59.6
SDA59: JP119.2, R179.1, U60.6
SDA60: JP121.2, R182.1, U61.6
SDA61: JP123.2, R185.1, U62.6
SDA62: JP125.2, R188.1, U63.6
SDA63: JP127.2, R191.1, U64.6
VCC: C1.1, JP5.3, SJ1.2, SJ2.1, U1.1
VCC1: C2.1, JP1.3, SJ3.2, SJ4.1, U2.1
VCC2: C3.1, JP3.3, SJ5.2, SJ6.1, U3.1
VCC3: C4.1, JP7.3, SJ7.2, SJ8.1, U4.1
VCC4: C5.1, JP9.3, SJ9.2, SJ10.1, U5.1
VCC5: C6.1, JP11.3, SJ11.2, SJ12.1, U6.1
VCC6: C7.1, JP13.3, SJ13.2, SJ14.1, U7.1
VCC7: C8.1, JP15.3, SJ15.2, SJ16.1, U8.1
VCC8: C9.1, JP17.3, SJ17.2, SJ18.1, U9.1
VCC9: C10.1, JP19.3, SJ19.2, SJ20.1, U10.1
VCC10: C11.1, JP21.3, SJ21.2, SJ22.1, U11.1
VCC11: C12.1, JP23.3, SJ23.2, SJ24.1, U12.1
VCC12: C13.1, JP25.3, SJ25.2, SJ26.1, U13.1
VCC13: C14.1, JP27.3, SJ27.2, SJ28.1, U14.1
VCC14: C15.1, JP29.3, SJ29.2, SJ30.1, U15.1
VCC15: C16.1, JP31.3, SJ31.2, SJ32.1, U16.1
VCC16: C17.1, JP33.3, SJ33.2, SJ34.1, U17.1
VCC17: C18.1, JP35.3, SJ35.2, SJ36.1, U18.1
VCC18: C19.1, JP37.3, SJ37.2, SJ38.1, U19.1
VCC19: C20.1, JP39.3, SJ39.2, SJ40.1, U20.1
VCC20: C21.1, JP41.3, SJ41.2, SJ42.1, U21.1
VCC21: C22.1, JP43.3, SJ43.2, SJ44.1, U22.1
VCC22: C23.1, JP45.3, SJ45.2, SJ46.1, U23.1
VCC23: C24.1, JP47.3, SJ47.2, SJ48.1, U24.1
VCC24: C25.1, JP49.3, SJ49.2, SJ50.1, U25.1
VCC25: C26.1, JP51.3, SJ51.2, SJ52.1, U26.1
VCC26: C27.1, JP53.3, SJ53.2, SJ54.1, U27.1
VCC27: C28.1, JP55.3, SJ55.2, SJ56.1, U28.1
VCC28: C29.1, JP57.3, SJ57.2, SJ58.1, U29.1
VCC29: C30.1, JP59.3, SJ59.2, SJ60.1, U30.1
VCC30: C31.1, JP61.3, SJ61.2, SJ62.1, U31.1
VCC31: C32.1, JP63.3, SJ63.2, SJ64.1, U32.1
VCC32: C33.1, JP65.3, SJ65.2, SJ66.1, U33.1
VCC33: C34.1, JP67.3, SJ67.2, SJ68.1, U34.1
VCC34: C35.1, JP69.3, SJ69.2, SJ70.1, U35.1
VCC35: C36.1, JP71.3, SJ71.2, SJ72.1, U36.1
VCC36: C37.1, JP73.3, SJ73.2, SJ74.1, U37.1
VCC37: C38.1, JP75.3, SJ75.2, SJ76.1, U38.1
VCC38: C39.1, JP77.3, SJ77.2, SJ78.1, U39.1
VCC39: C40.1, JP79.3, SJ79.2, SJ80.1, U40.1
VCC40: C41.1, JP81.3, SJ81.2, SJ82.1, U41.1
VCC41: C42.1, JP83.3, SJ83.2, SJ84.1, U42.1
VCC42: C43.1, JP85.3, SJ85.2, SJ86.1, U43.1
VCC43: C44.1, JP87.3, SJ87.2, SJ88.1, U44.1
VCC44: C45.1, JP89.3, SJ89.2, SJ90.1, U45.1
VCC45: C46.1, JP91.3, SJ91.2, SJ92.1, U46.1
VCC46: C47.1, JP93.3, SJ93.2, SJ94.1, U47.1
VCC47: C48.1, JP95.3, SJ95.2, SJ96.1, U48.1
VCC48: C49.1, JP97.3, SJ97.2, SJ98.1, U49.1
VCC49: C50.1, JP99.3, SJ99.2, SJ100.1, U50.1
VCC50: C51.1, JP101.3, SJ101.2, SJ102.1, U51.1
VCC51: C52.1, JP103.3, SJ103.2, SJ104.1, U52.1
VCC52: C53.1, JP105.3, SJ105.2, SJ106.1, U53.1
VCC53: C54.1, JP107.3, SJ107.2, SJ108.1, U54.1
VCC54: C55.1, JP109.3, SJ109.2, SJ110.1, U55.1
VCC55: C56.1, JP111.3, SJ111.2, SJ112.1, U56.1
VCC56: C57.1, JP113.3, SJ113.2, SJ114.1, U57.1
VCC57: C58.1, JP115.3, SJ115.2, SJ116.1, U58.1
VCC58: C59.1, JP117.3, SJ117.2, SJ118.1, U59.1
VCC59: C60.1, JP119.3, SJ119.2, SJ120.1, U60.1
VCC60: C61.1, JP121.3, SJ121.2, SJ122.1, U61.1
VCC61: C62.1, JP123.3, SJ123.2, SJ124.1, U62.1
VCC62: C63.1, JP125.3, SJ125.2, SJ126.1, U63.1
VCC63: C64.1, JP127.3, SJ127.2, SJ128.1, U64.1
VOUT: JP6.2, U1.3
VOUT1: JP2.2, U2.3
VOUT2: JP4.2, U3.3
VOUT3: JP8.2, U4.3
VOUT4: JP10.2, U5.3
VOUT5: JP12.2, U6.3
VOUT6: JP14.2, U7.3
VOUT7: JP16.2, U8.3
VOUT8: JP18.2, U9.3
VOUT9: JP20.2, U10.3
VOUT10: JP22.2, U11.3
VOUT11: JP24.2, U12.3
VOUT12: JP26.2, U13.3
VOUT13: JP28.2, U14.3
VOUT14: JP30.2, U15.3
VOUT15: JP32.2, U16.3
VOUT16: JP34.2, U17.3
VOUT17: JP36.2, U18.3
VOUT18: JP38.2, U19.3
VOUT19: JP40.2, U20.3
VOUT20: JP42.2, U21.3
VOUT21: JP44.2, U22.3
VOUT22: JP46.2, U23.3
VOUT23: JP48.2, U24.3
VOUT24: JP50.2, U25.3
VOUT25: JP52.2, U26.3
VOUT26: JP54.2, U27.3
VOUT27: JP56.2, U28.3
VOUT28: JP58.2, U29.3
VOUT29: JP60.2, U30.3
VOUT30: JP62.2, U31.3
VOUT31: JP64.2, U32.3
VOUT32: JP66.2, U33.3
VOUT33: JP68.2, U34.3
VOUT34: JP70.2, U35.3
VOUT35: JP72.2, U36.3
VOUT36: JP74.2, U37.3
VOUT37: JP76.2, U38.3
VOUT38: JP78.2, U39.3
VOUT39: JP80.2, U40.3
VOUT40: JP82.2, U41.3
VOUT41: JP84.2, U42.3
VOUT42: JP86.2, U43.3
VOUT43: JP88.2, U44.3
VOUT44: JP90.2, U45.3
VOUT45: JP92.2, U46.3
VOUT46: JP94.2, U47.3
VOUT47: JP96.2, U48.3
VOUT48: JP98.2, U49.3
VOUT49: JP100.2, U50.3
VOUT50: JP102.2, U51.3
VOUT51: JP104.2, U52.3
VOUT52: JP106.2, U53.3
VOUT53: JP108.2, U54.3
VOUT54: JP110.2, U55.3
VOUT55: JP112.2, U56.3
VOUT56: JP114.2, U57.3
VOUT57: JP116.2, U58.3
VOUT58: JP118.2, U59.3
VOUT59: JP120.2, U60.3
VOUT60: JP122.2, U61.3
VOUT61: JP124.2, U62.3
VOUT62: JP126.2, U63.3
VOUT63: JP128.2, U64.3

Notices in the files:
parts and their libraries:
SparkFun-AnalogIC: Licensing:Creative Commons ShareAlike 4.0 International - https://creativecommons.org/licenses/by-sa/4.0
SparkFun-Aesthetics: Released under the Creative Commons Attribution Share-Alike 4.0 License
SparkFun-Aesthetics: Released under the Creative Commons
